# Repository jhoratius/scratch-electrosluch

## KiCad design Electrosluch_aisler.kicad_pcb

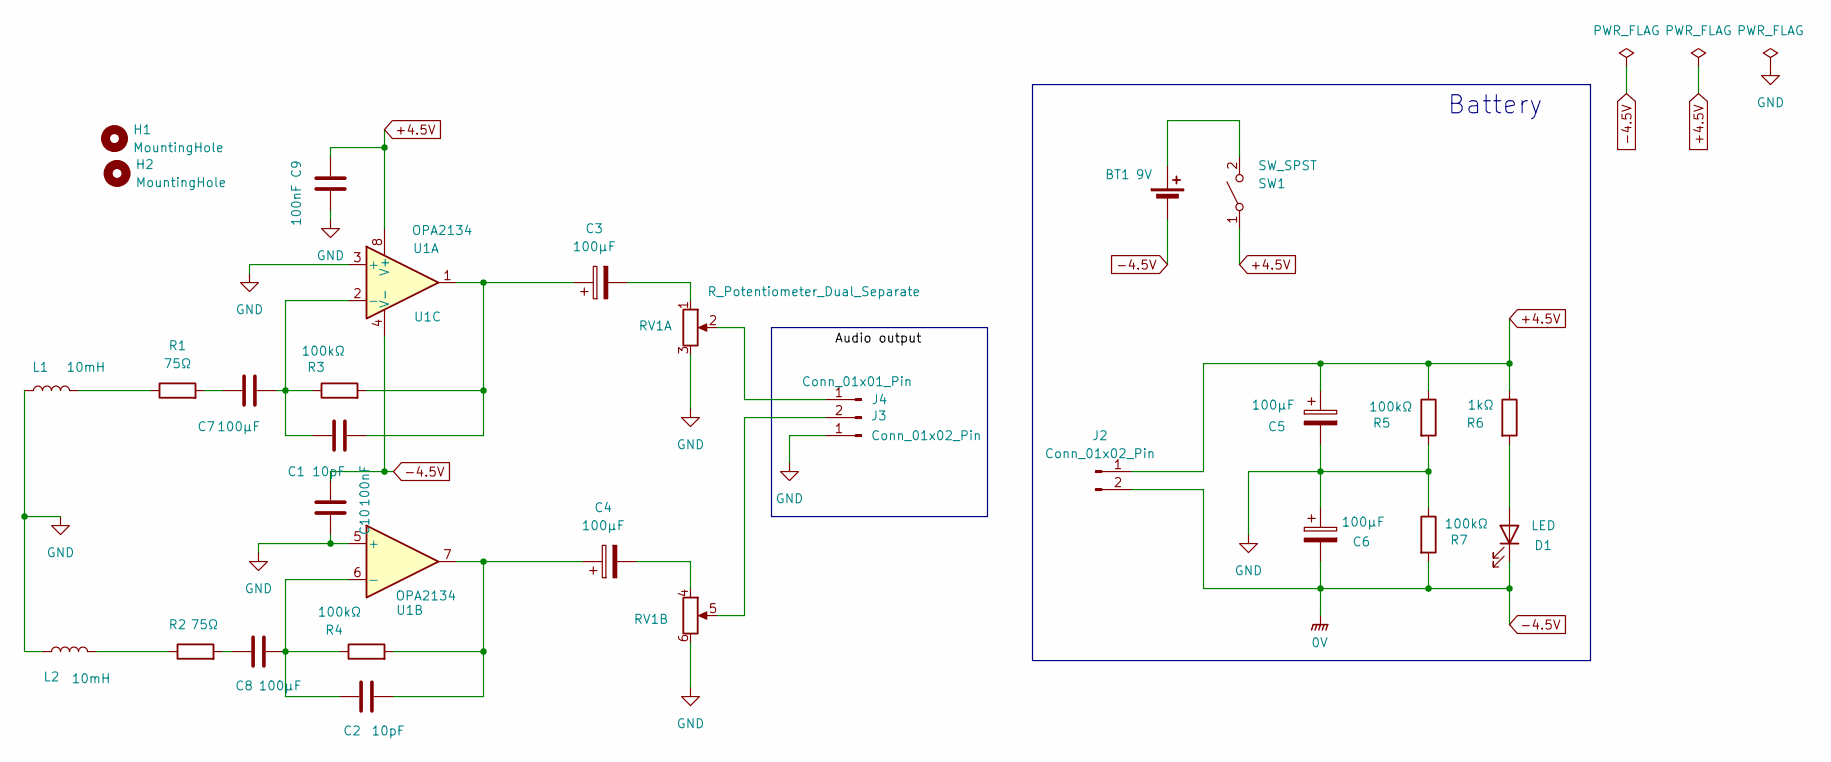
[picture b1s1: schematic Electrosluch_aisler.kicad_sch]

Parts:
BT1: 9V
C1, C2: 10pF; C_Disc_D5.0mm_W2.5mm_P2.50mm
C3, C4, C5, C6, C7, C8: 100µF; CP_Radial_D6.3mm_P2.50mm
C9, C10: 100nF; C_Disc_D5.0mm_W2.5mm_P2.50mm
D1: LED; LED_D5.0mm
H1, H2: MountingHole; MountingHole_4mm
J2: Conn_01x02_Pin; PinSocket_1x02_P2.54mm_Vertical
J3: Conn_01x02_Pin; PinHeader_1x02_P2.54mm_Vertical
J4: Conn_01x01_Pin; PinSocket_1x01_P2.54mm_Vertical
L1, L2: 10mH; R_LDR_7x6mm_P5.1mm_Vertical
R1, R2: 75Ω; R_Axial_DIN0207_L6.3mm_D2.5mm_P10.16mm_Horizontal
R3, R4, R5, R7: 100kΩ; R_Axial_DIN0207_L6.3mm_D2.5mm_P10.16mm_Horizontal
R6: 1kΩ; R_Axial_DIN0207_L6.3mm_D2.5mm_P10.16mm_Horizontal
RV1: R_Potentiometer_Dual_Separate; Potentiometer_Alps_RK097_Dual_Horizontal
SW1: SW_SPST; PinHeader_1x02_P2.54mm_Vertical
U1: OPA2134; DIP-8_W7.62mm_LongPads

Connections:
+4.5V: C5.1, C9.1, J2.1, R5.1, R6.1, SW1.1 (A), U1.8 (V+)
-4.5V: BT1.2 (-), C6.2, C10.2, D1.1 (K), J2.2, R7.2, U1.4 (V-)
GND: C5.2, C6.1, C9.2, C10.1, J3.1, L1.1, L2.1, R5.2, R7.1, RV1.3, RV1.6, U1.3 (+), U1.5 (+)
unnamed: BT1.1 (+), SW1.2 (B)
unnamed: C1.2, C3.1, R3.2, U1.1
unnamed: C2.2, C4.1, R4.2, U1.7
unnamed: C3.2, RV1.1
unnamed: C4.2, RV1.4
unnamed: C7.1, R1.2
unnamed: C8.1, R2.2
unnamed: D1.2 (A), R6.2
unnamed: J3.2, RV1.5
unnamed: J4.1 (Pin_1_1), RV1.2
unnamed: L1.2, R1.1
unnamed: L2.2, R2.1
unnamed: C1.1, C7.2, R3.1, U1.2 (-)
unnamed: C2.1, C8.2, R4.1, U1.6 (-)

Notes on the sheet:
Battery

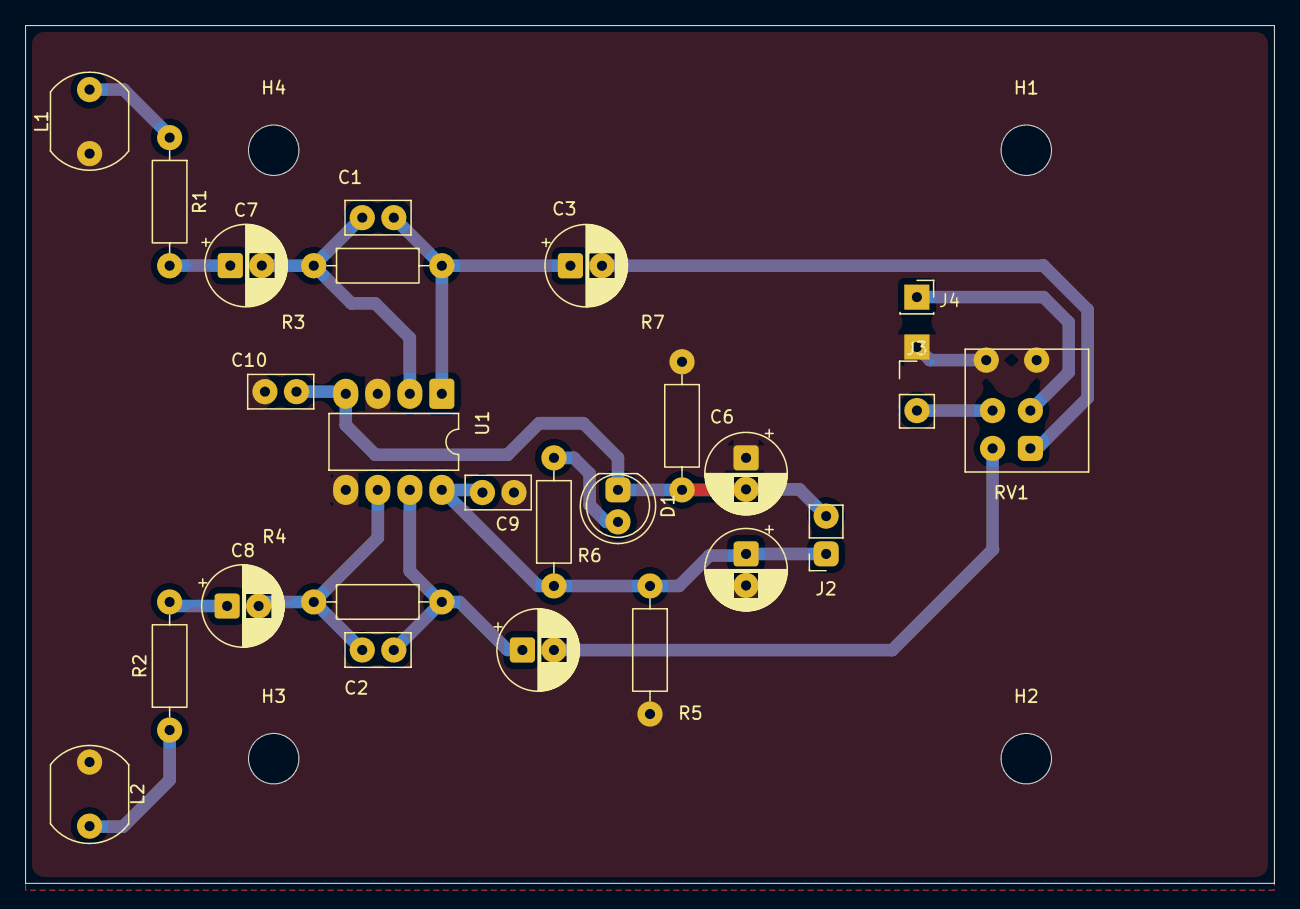
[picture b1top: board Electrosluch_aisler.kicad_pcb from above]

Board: 2 copper layers, 99.1 x 68.0 mm, 29 parts (0 on the bottom side), 16 nets.

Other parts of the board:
H3, H4: MountingHole; MountingHole_4mm
